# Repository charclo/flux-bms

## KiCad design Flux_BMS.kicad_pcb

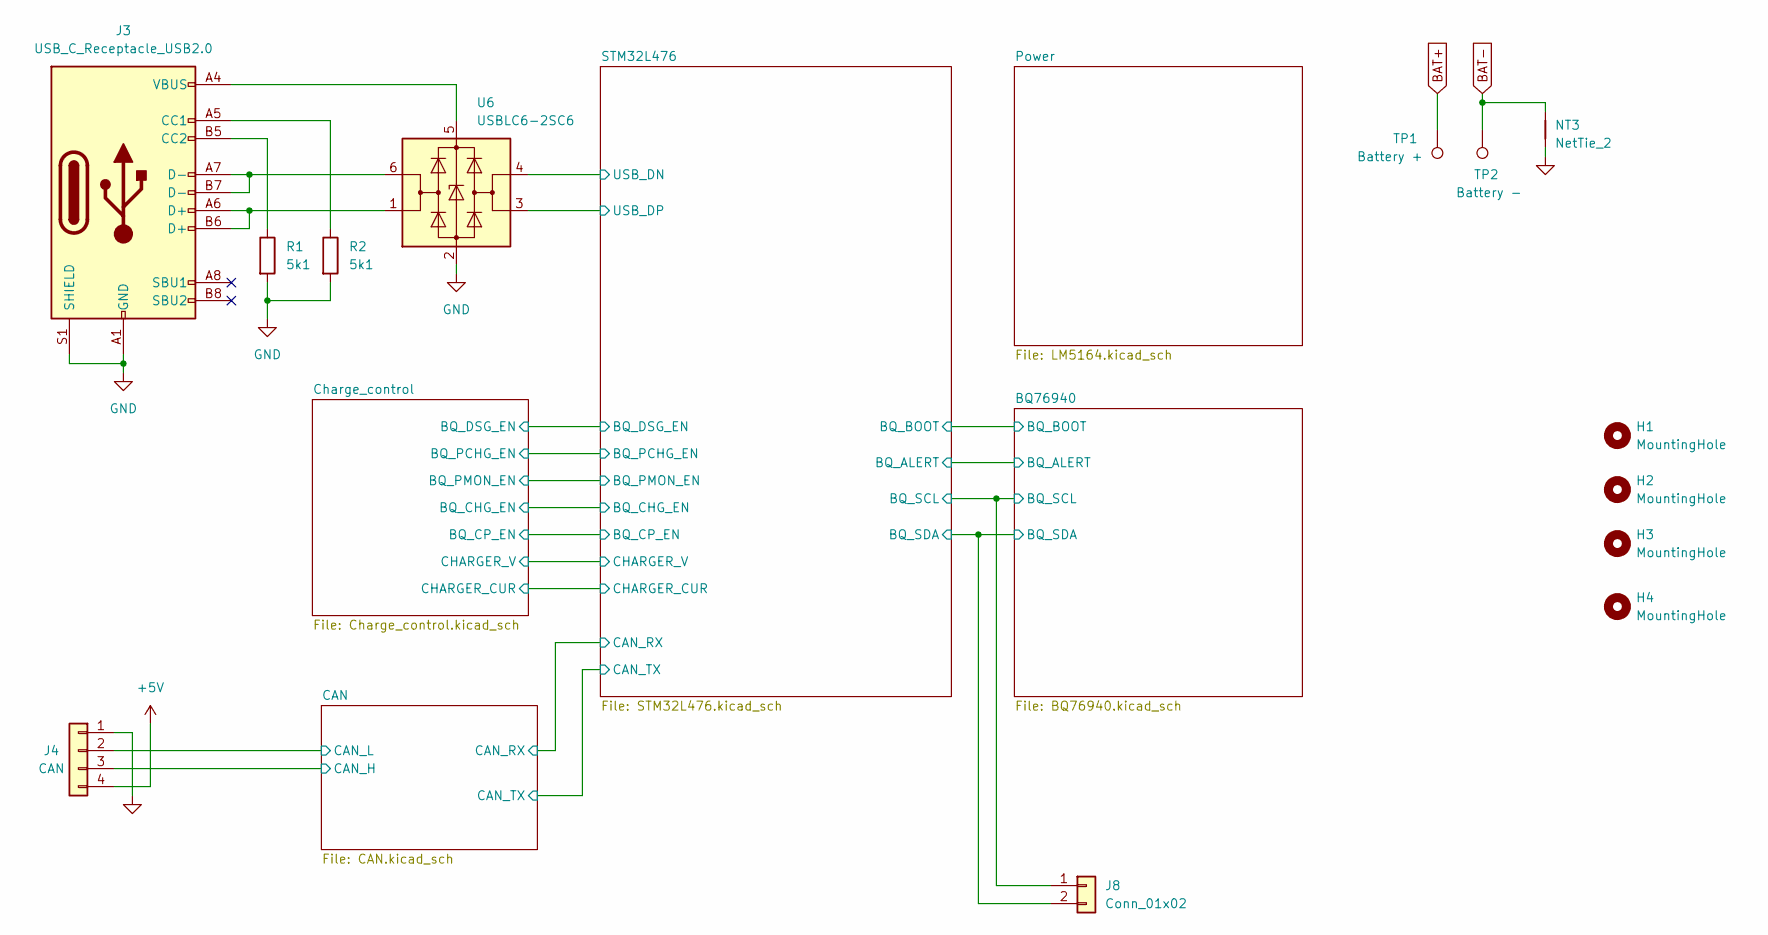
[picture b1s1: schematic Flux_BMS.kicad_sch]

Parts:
H1, H2, H3, H4: MountingHole; MountingHole_3.2mm_M3
J3: USB_C_Receptacle_USB2.0; USB_C_Receptacle_HRO_TYPE-C-31-M-12
J4: CAN; JST_PH_B4B-PH-K_1x04_P2.00mm_Vertical
J8: Conn_01x02; PinHeader_1x02_P2.54mm_Vertical
NT3: NetTie_2; NetTie-2_SMD_Pad2.0mm
R1, R2: 5k1; R_0805_2012Metric; LCSC C27834
TP1: Battery +; PAD
TP2: Battery -; PAD
U6: USBLC6-2SC6; SOT-23-6; LCSC C2827654

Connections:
+5V: J4.4; also elsewhere on the board
/BQ76940/BQ_SCL: J8.1; also elsewhere on the board
/BQ76940/BQ_SDA: J8.2; also elsewhere on the board
/CAN/CAN_H: J4.3; also elsewhere on the board
/CAN/CAN_L: J4.2; also elsewhere on the board
/STM32L476/USB_DN: U6.4 (I/O2); also elsewhere on the board
/STM32L476/USB_DP: U6.3 (I/O2); also elsewhere on the board
BAT+: TP1.1; also elsewhere on the board
BAT-: NT3.2, TP2.1; also elsewhere on the board
unnamed: J3.A5 (CC1), R2.1
unnamed: J3.B5 (CC2), R1.1
unnamed: J3.A6 (D+), J3.B6 (D+), U6.1 (I/O1)
unnamed: J3.A7 (D-), J3.B7 (D-), U6.6 (I/O1)
unnamed: J3.A4 (VBUS), J3.A9 (VBUS), J3.B4 (VBUS), J3.B9 (VBUS), U6.5 (VBUS)

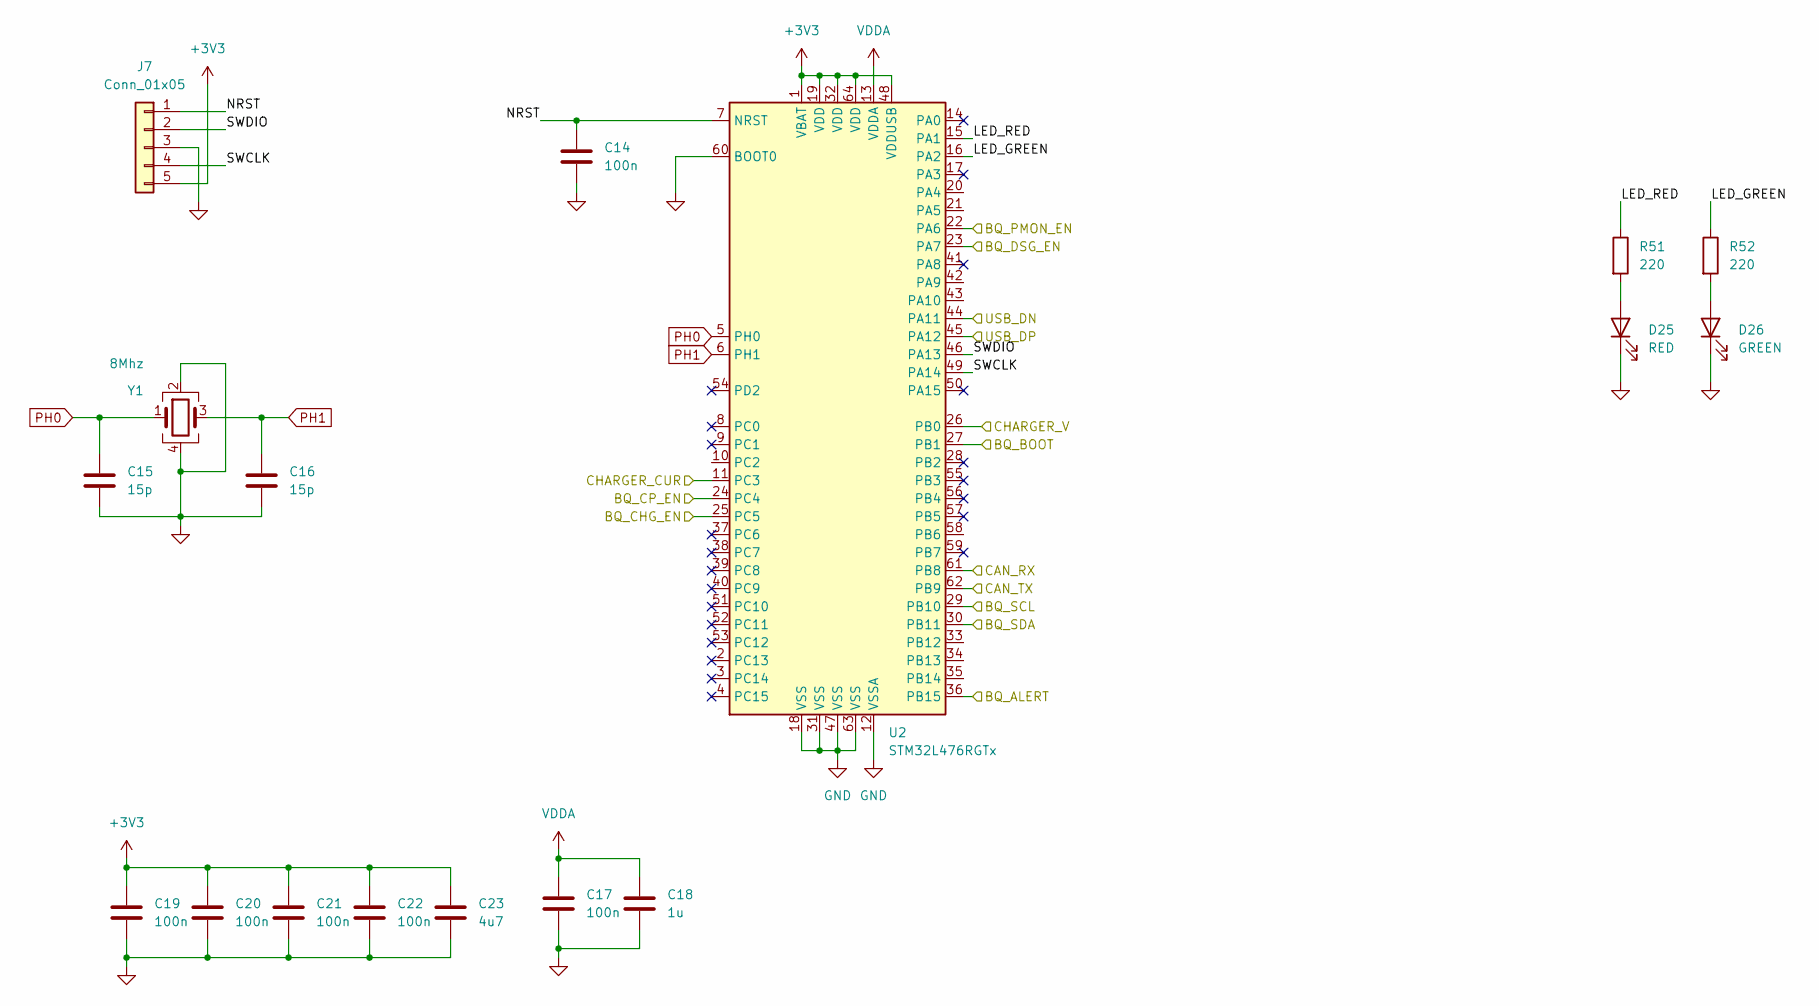
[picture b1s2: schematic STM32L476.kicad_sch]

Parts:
C14, C17, C19, C20, C21, C22: 100n; C_0603_1608Metric; LCSC C14663
C15, C16: 15p; C_0603_1608Metric; LCSC C1644
C18: 1u; C_0603_1608Metric; LCSC C15849
C23: 4u7; C_0603_1608Metric; LCSC C19666
D25: RED; LED_0805_2012Metric; LCSC C84256
D26: GREEN; LED_0805_2012Metric; LCSC C84256
J7: Conn_01x05; JST_PH_B5B-PH-K_1x05_P2.00mm_Vertical
R51, R52: 220; R_0805_2012Metric; LCSC C17557
U2: STM32L476RGTx; LQFP-64_10x10mm_P0.5mm; LCSC C92468
Y1: 8Mhz; Crystal_SMD_3225-4Pin_3.2x2.5mm; LCSC C2924619

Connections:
+3V3: C19.1, C20.1, C21.1, C22.1, C23.1, J7.5, U2.1 (VBAT), U2.19 (VDD), U2.32 (VDD), U2.48 (VDDUSB), U2.64 (VDD); also elsewhere on the board
/BQ76940/BQ_ALERT: U2.36 (PB15); also elsewhere on the board
/BQ76940/BQ_BOOT: U2.27 (PB1); also elsewhere on the board
/BQ76940/BQ_SCL: U2.29 (PB10); also elsewhere on the board
/BQ76940/BQ_SDA: U2.30 (PB11); also elsewhere on the board
/CAN/CAN_RX: U2.61 (PB8); also elsewhere on the board
/CAN/CAN_TX: U2.62 (PB9); also elsewhere on the board
/Charge_control/BQ_CHG_EN: U2.25 (PC5); also elsewhere on the board
/Charge_control/BQ_CP_EN: U2.24 (PC4); also elsewhere on the board
/Charge_control/BQ_DSG_EN: U2.23 (PA7); also elsewhere on the board
/Charge_control/BQ_PMON_EN: U2.22 (PA6); also elsewhere on the board
/Charge_control/CHARGER_CUR: U2.11 (PC3); also elsewhere on the board
/Charge_control/CHARGER_V: U2.26 (PB0); also elsewhere on the board
/STM32L476/LED_GREEN: R52.1, U2.16 (PA2)
/STM32L476/LED_RED: R51.1, U2.15 (PA1)
/STM32L476/NRST: C14.1, J7.1, U2.7 (NRST)
/STM32L476/SWCLK: J7.4, U2.49 (PA14)
/STM32L476/SWDIO: J7.2, U2.46 (PA13)
/STM32L476/USB_DN: U2.44 (PA11); also elsewhere on the board
/STM32L476/USB_DP: U2.45 (PA12); also elsewhere on the board
unnamed: D25.2 (A), R51.2
unnamed: D26.2 (A), R52.2
PH0: C15.1, U2.5 (PH0), Y1.1
PH1: C16.1, U2.6 (PH1), Y1.3
VDDA: C17.1, C18.1, U2.13 (VDDA)

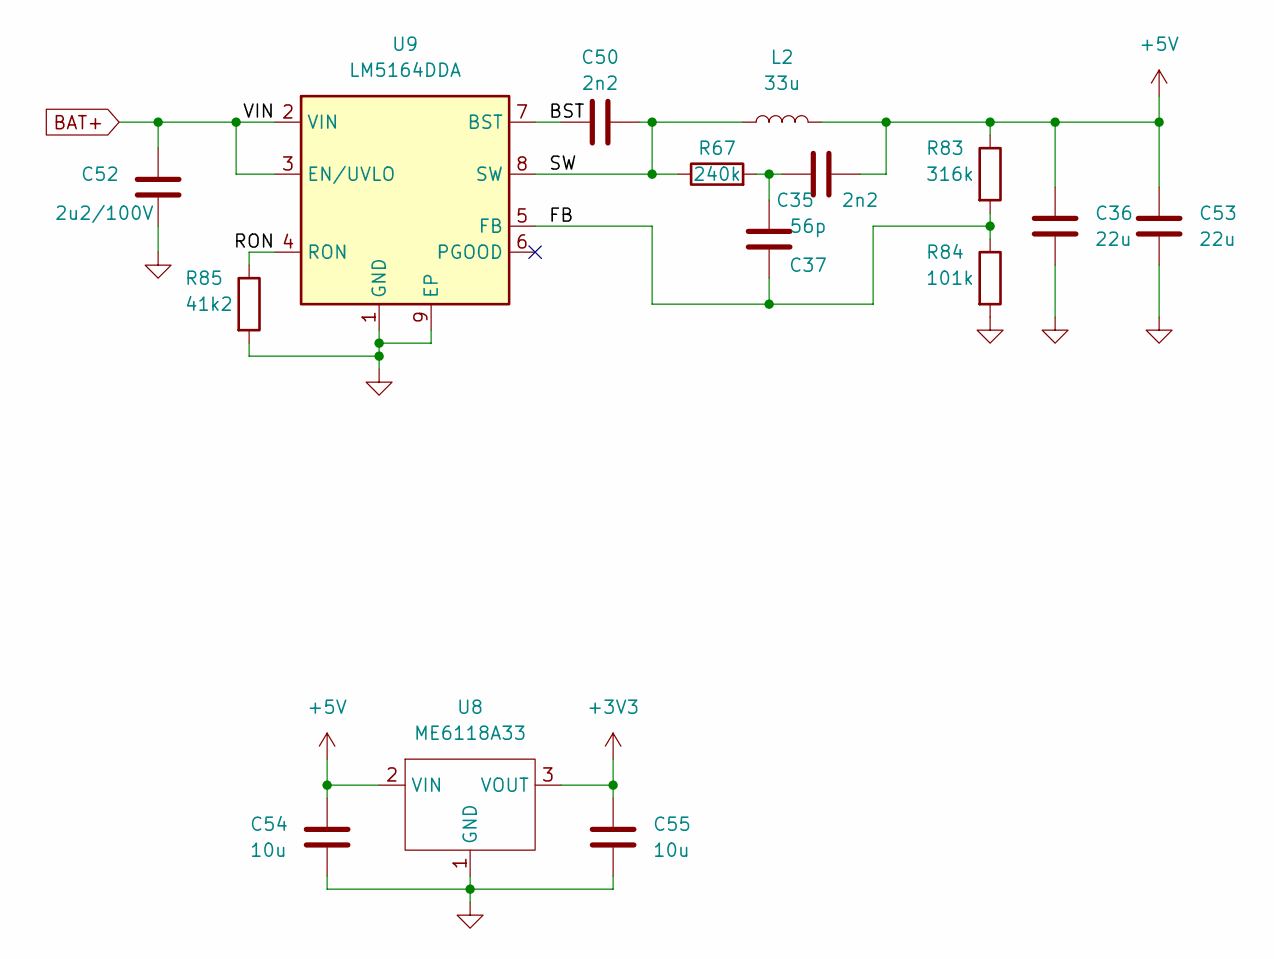
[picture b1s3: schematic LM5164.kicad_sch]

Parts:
C35, C50: 2n2; C_0603_1608Metric; LCSC C1604
C36, C53: 22u; C_0805_2012Metric; LCSC C45783
C37: 56p; C_0805_2012Metric; LCSC C14857
C52: 2u2/100V; C_1206_3216Metric; LCSC C577211
C54, C55: 10u; C_0805_2012Metric; LCSC C440198
L2: 33u; L_Taiyo-Yuden_NR-80xx
R67: 240k; R_0805_2012Metric; LCSC C416833
R83: 316k; R_0805_2012Metric; LCSC C367975
R84: 101k; R_0805_2012Metric; LCSC C17719
R85: 41k2; R_0805_2012Metric; LCSC C149504
U8: ME6118A33; SOT-89-3; LCSC C236721
U9: LM5164DDA; HSOP-8-1EP_3.9x4.9mm_P1.27mm_EP2.41x3.1mm_ThermalVias; LCSC C477928

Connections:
+3V3: C55.1, U8.3 (VOUT); also elsewhere on the board
+5V: C35.2, C36.1, C53.1, C54.1, L2.2, R83.1, U8.2 (VIN); also elsewhere on the board
/Power/BST: C50.1, U9.7 (BST)
/Power/FB: C37.1, R83.2, R84.1, U9.5 (FB)
/Power/RON: R85.1, U9.4 (RON)
/Power/SW: C50.2, L2.1, R67.1, U9.8 (SW)
BAT+: C52.1, U9.2 (VIN), U9.3 (EN/UVLO); also elsewhere on the board
unnamed: C35.1, C37.2, R67.2

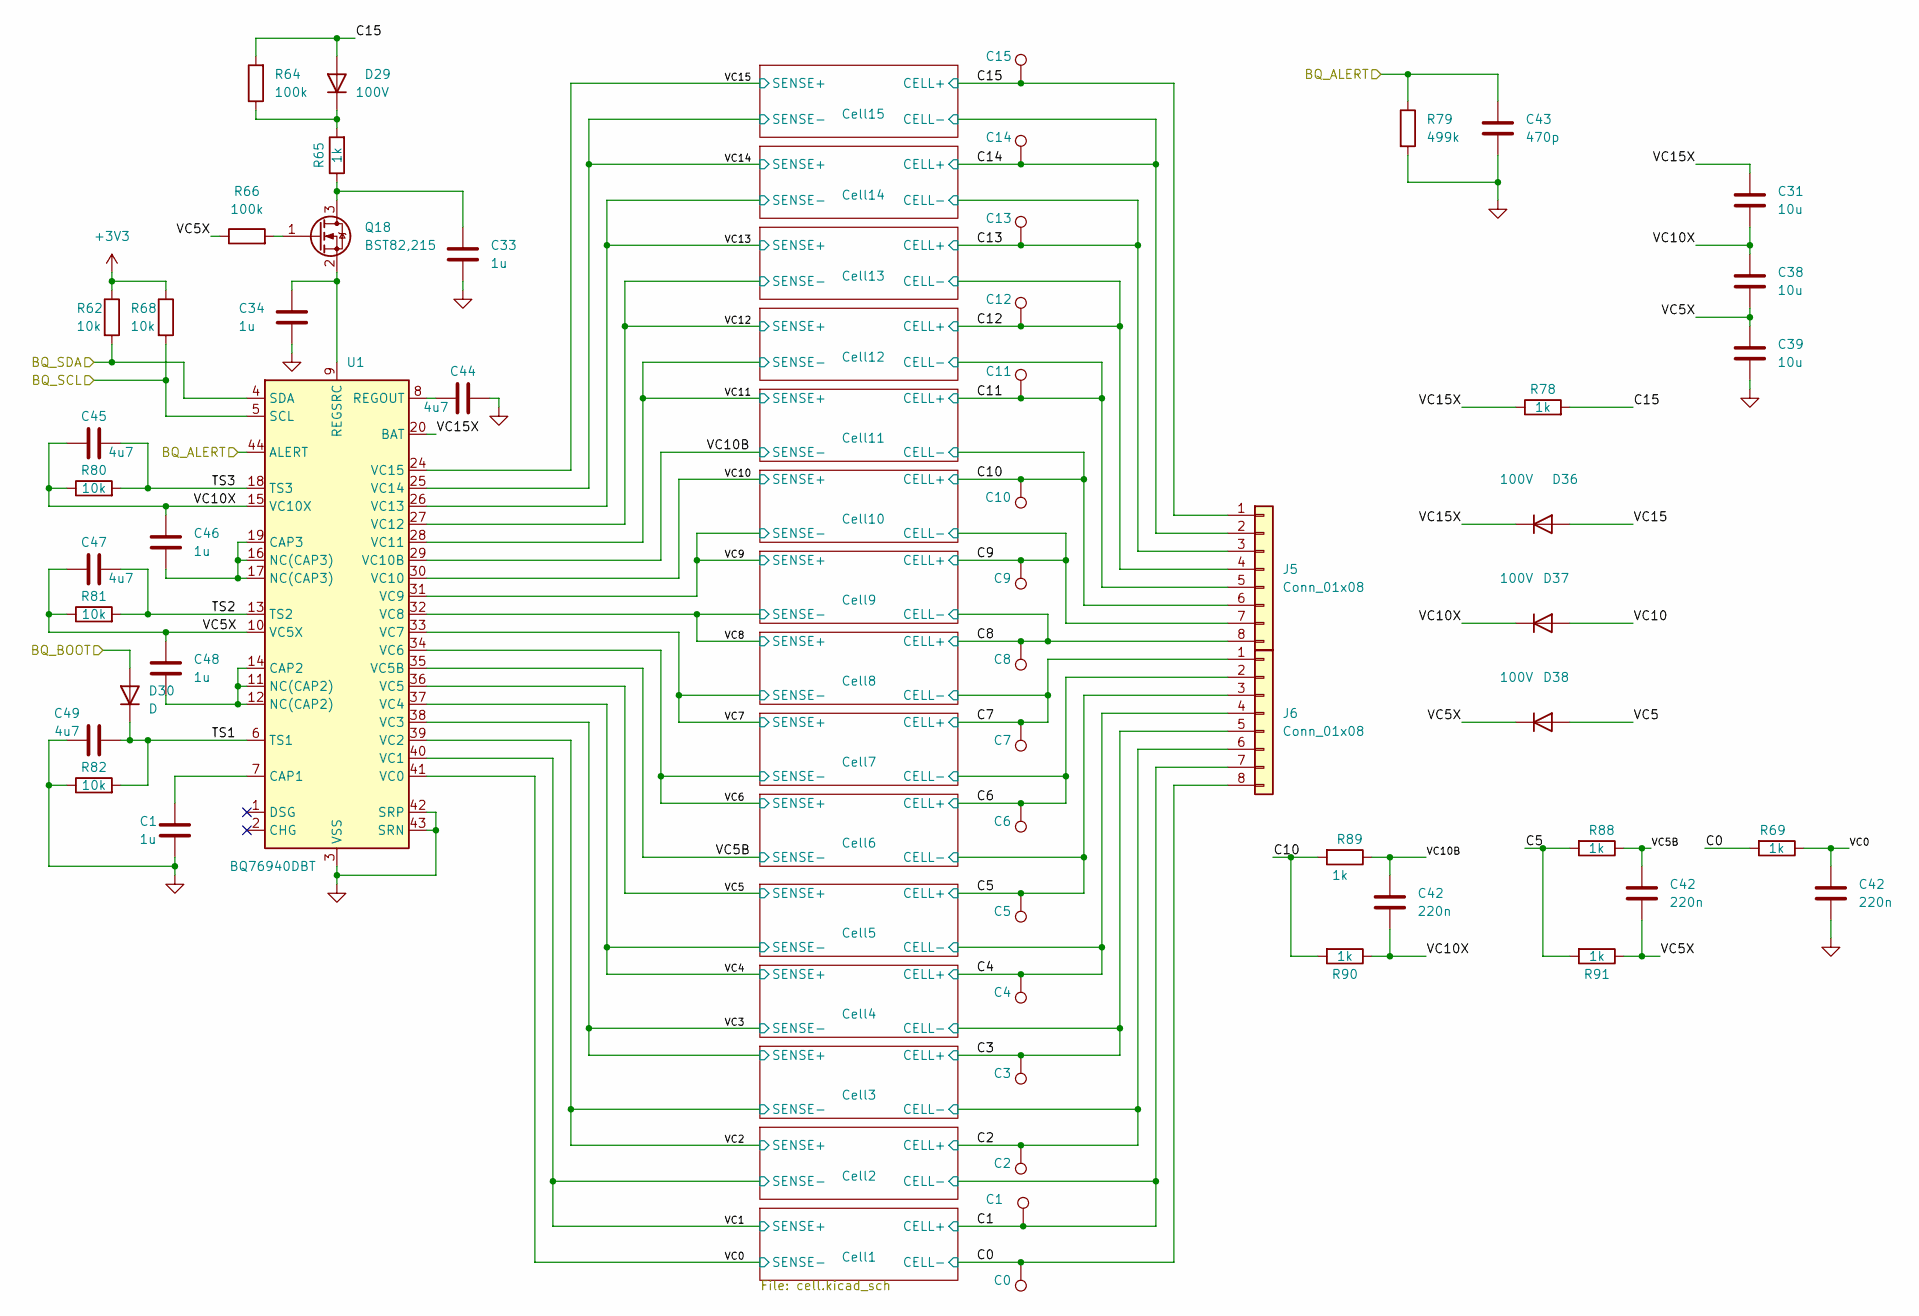
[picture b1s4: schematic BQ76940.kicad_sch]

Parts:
C1, C33, C34, C46, C48: 1u; C_0805_2012Metric; LCSC C28323
C31, C38, C39: 10u; C_0805_2012Metric; LCSC C440198
C42: 220n; C_0805_2012Metric; LCSC C5378
C43: 470p; C_0805_2012Metric; LCSC C1743
C44, C45, C47, C49: 4u7; C_0805_2012Metric; LCSC C440198
D29, D36, D37, D38: 100V; D_SOD-123; LCSC C83528
D30: D; D_SOD-323_HandSoldering
J5, J6: Conn_01x08; JST_PH_S8B-PH-K_1x08_P2.00mm_Horizontal
Q18: BST82,215; SOT-23; LCSC C426800
R62, R68, R82: 10k; R_0805_2012Metric; LCSC C17414
R64, R66: 100k; R_0805_2012Metric; LCSC C149504
R65, R69, R78, R88, R89, R90, R91: 1k; R_0805_2012Metric; LCSC C17513
R79: 499k; R_0805_2012Metric; LCSC C2960934
R80, R81: 10k; JST_PH_B2B-PH-K_1x02_P2.00mm_Vertical
TP7: C15; TestPoint_THTPad_D1.0mm_Drill0.5mm
TP8: C14; TestPoint_THTPad_D1.0mm_Drill0.5mm
TP9: C13; TestPoint_THTPad_D1.0mm_Drill0.5mm
TP10: C12; TestPoint_THTPad_D1.0mm_Drill0.5mm
TP11: C11; TestPoint_THTPad_D1.0mm_Drill0.5mm
TP12: C10; TestPoint_THTPad_D1.0mm_Drill0.5mm
TP13: C9; TestPoint_THTPad_D1.0mm_Drill0.5mm
TP14: C8; TestPoint_THTPad_D1.0mm_Drill0.5mm
TP15: C7; TestPoint_THTPad_D1.0mm_Drill0.5mm
TP16: C6; TestPoint_THTPad_D1.0mm_Drill0.5mm
TP17: C5; TestPoint_THTPad_D1.0mm_Drill0.5mm
TP18: C4; TestPoint_THTPad_D1.0mm_Drill0.5mm
TP19: C3; TestPoint_THTPad_D1.0mm_Drill0.5mm
TP20: C2; TestPoint_THTPad_D1.0mm_Drill0.5mm
TP21: C1; TestPoint_THTPad_D1.0mm_Drill0.5mm
TP22: C0; TestPoint_THTPad_D1.0mm_Drill0.5mm
U1: BQ76940DBT; TSSOP-44_4.4x11.2mm_P0.5mm; LCSC C368606

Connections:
+3V3: R62.1, R68.1; also elsewhere on the board
/BQ76940/BQ_ALERT: C43.1, R79.1, U1.44 (ALERT); also elsewhere on the board
/BQ76940/BQ_BOOT: D30.2 (A); also elsewhere on the board
/BQ76940/BQ_SCL: R68.2, U1.5 (SCL); also elsewhere on the board
/BQ76940/BQ_SDA: R62.2, U1.4 (SDA); also elsewhere on the board
/BQ76940/C0: J6.8, R69.2, TP22.1; also elsewhere on the board
/BQ76940/C1: J6.7, TP21.1; also elsewhere on the board
/BQ76940/C2: J6.6, TP20.1; also elsewhere on the board
/BQ76940/C3: J6.5, TP19.1; also elsewhere on the board
/BQ76940/C4: J6.4, TP18.1; also elsewhere on the board
/BQ76940/C5: J6.3, R88.2, R91.2, TP17.1; also elsewhere on the board
/BQ76940/C6: J6.2, TP16.1; also elsewhere on the board
/BQ76940/C7: J6.1, TP15.1; also elsewhere on the board
/BQ76940/C8: J5.8, TP14.1; also elsewhere on the board
/BQ76940/C9: J5.7, TP13.1; also elsewhere on the board
/BQ76940/C10: J5.6, R89.2, R90.2, TP12.1; also elsewhere on the board
/BQ76940/C11: J5.5, TP11.1; also elsewhere on the board
/BQ76940/C12: J5.4, TP10.1; also elsewhere on the board
/BQ76940/C13: J5.3, TP9.1; also elsewhere on the board
/BQ76940/C14: J5.2, TP8.1; also elsewhere on the board
/BQ76940/C15: D29.2 (A), J5.1, R64.2, R78.2, TP7.1; also elsewhere on the board
/BQ76940/TS1: C49.2, D30.1 (K), R82.2, U1.6 (TS1)
/BQ76940/TS2: C47.2, R81.2, U1.13 (TS2)
/BQ76940/TS3: C45.2, R80.2, U1.18 (TS3)
/BQ76940/VC1: U1.40 (VC1); also elsewhere on the board
/BQ76940/VC2: U1.39 (VC2); also elsewhere on the board
/BQ76940/VC3: U1.38 (VC3); also elsewhere on the board
/BQ76940/VC4: U1.37 (VC4); also elsewhere on the board
/BQ76940/VC5: D38.2 (A), U1.36 (VC5); also elsewhere on the board
/BQ76940/VC6: U1.34 (VC6); also elsewhere on the board
/BQ76940/VC7: U1.33 (VC7); also elsewhere on the board
/BQ76940/VC8: U1.32 (VC8); also elsewhere on the board
/BQ76940/VC9: U1.31 (VC9); also elsewhere on the board
/BQ76940/VC10: D37.2 (A), U1.30 (VC10); also elsewhere on the board
/BQ76940/VC11: U1.28 (VC11); also elsewhere on the board
/BQ76940/VC12: U1.27 (VC12); also elsewhere on the board
/BQ76940/VC13: U1.26 (VC13); also elsewhere on the board
/BQ76940/VC15X: C31.1, D36.1 (K), R78.1, U1.20 (BAT)
unnamed: D29.1 (K), R64.1, R65.2
unnamed: C33.1, Q18.3 (D), R65.1
unnamed: Q18.1 (G), R66.2
unnamed: C34.1, Q18.2 (S), U1.9 (REGSRC)
unnamed: C1.1, U1.7 (CAP1)
unnamed: C48.2, U1.11 (NC(CAP2)), U1.12 (NC(CAP2)), U1.14 (CAP2)
unnamed: C46.2, U1.16 (NC(CAP3)), U1.17 (NC(CAP3)), U1.19 (CAP3)
unnamed: C44.1, U1.8 (REGOUT)

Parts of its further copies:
C2, C3, C4, C5, C6, C7, C8, C9, C10, C11, C12, C13, C24, C41, C51, C56, C57: 220n; C_0805_2012Metric; LCSC C5378

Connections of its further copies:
/BQ76940/VC1: C10.2, C11.1; also elsewhere on the board
/BQ76940/VC2: C9.2, C10.1; also elsewhere on the board
/BQ76940/VC3: C9.1, C24.2; also elsewhere on the board
/BQ76940/VC4: C7.2, C24.1; also elsewhere on the board
/BQ76940/VC5: C7.1; also elsewhere on the board
/BQ76940/VC6: C5.2, C6.1; also elsewhere on the board
/BQ76940/VC7: C4.2, C5.1; also elsewhere on the board
/BQ76940/VC8: C3.2, C4.1; also elsewhere on the board
/BQ76940/VC9: C2.2, C3.1; also elsewhere on the board
/BQ76940/VC10: C2.1; also elsewhere on the board
/BQ76940/VC11: C8.2, C13.1; also elsewhere on the board
/BQ76940/VC12: C8.1, C12.2; also elsewhere on the board
/BQ76940/VC13: C12.1, C41.2; also elsewhere on the board

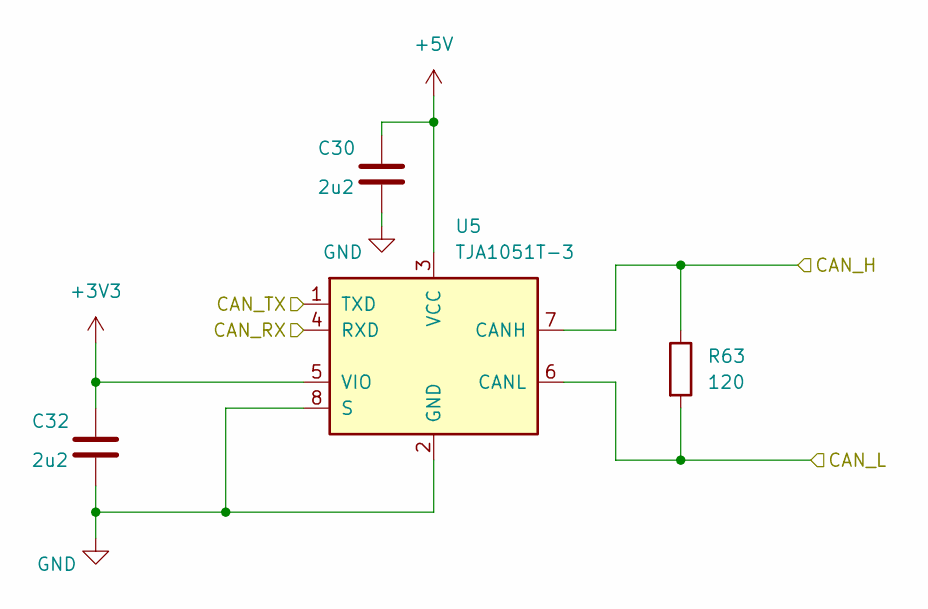
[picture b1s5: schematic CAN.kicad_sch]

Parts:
C30, C32: 2u2; C_0603_1608Metric; LCSC C23630
R63: 120; R_0805_2012Metric; LCSC C17437
U5: TJA1051T-3; SOIC-8_3.9x4.9mm_P1.27mm; LCSC c58988

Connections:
+3V3: C32.1, U5.5 (VIO); also elsewhere on the board
+5V: C30.1, U5.3 (VCC); also elsewhere on the board
/CAN/CAN_H: R63.1, U5.7 (CANH); also elsewhere on the board
/CAN/CAN_L: R63.2, U5.6 (CANL); also elsewhere on the board
/CAN/CAN_RX: U5.4 (RXD); also elsewhere on the board
/CAN/CAN_TX: U5.1 (TXD); also elsewhere on the board

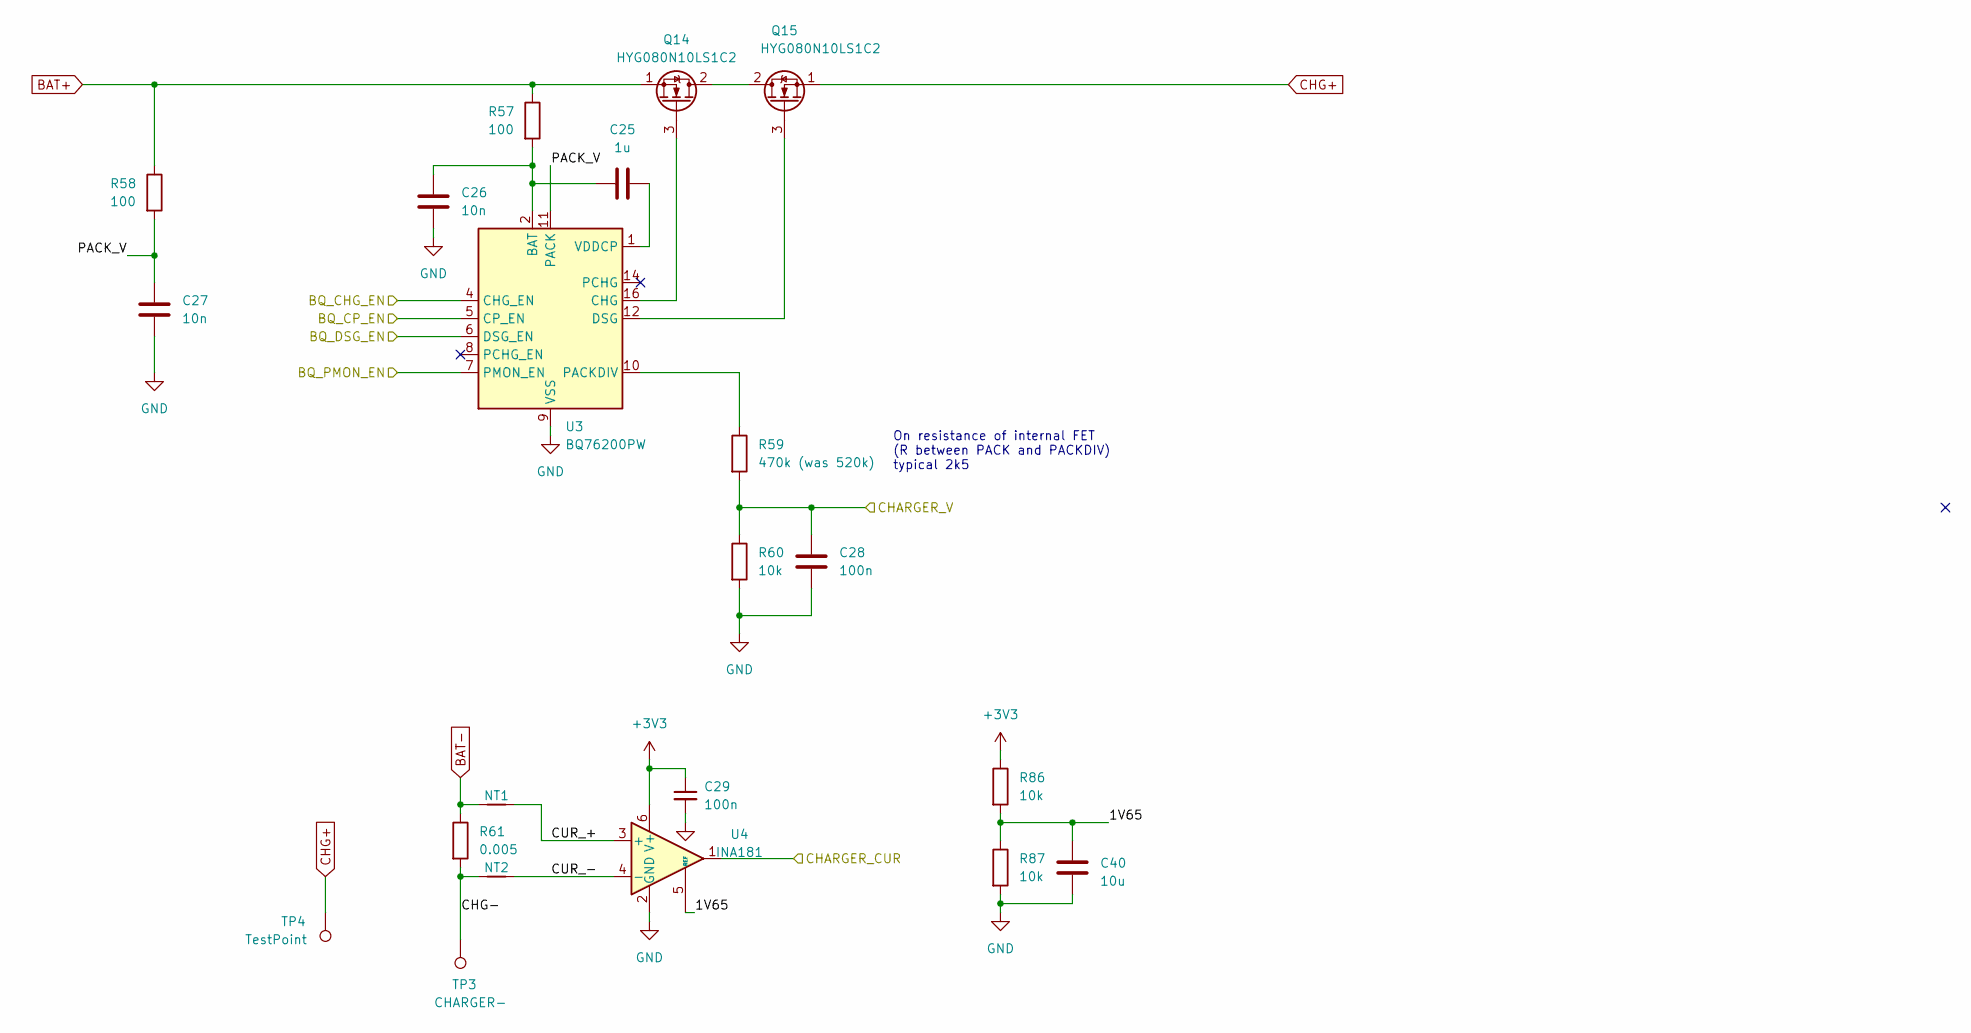
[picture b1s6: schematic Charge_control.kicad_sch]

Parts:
C25: 1u; C_0603_1608Metric; LCSC C15849
C26: 10n; C_0603_1608Metric; LCSC C57112
C27: 10n; C_0805_2012Metric; LCSC C1710
C28: 100n; C_0805_2012Metric; LCSC C28233
C29: 100n; C_0603_1608Metric; LCSC C14663
C40: 10u; C_0805_2012Metric; LCSC C440198
NT1, NT2: NetTie_2; NetTie-2_SMD_Pad0.5mm
Q14, Q15: HYG080N10LS1C2; TRANS_BSC076N06NS3-G; LCSC C3011225
R57, R58: 100; R_0805_2012Metric; LCSC C17408
R59: 470k (was 520k); R_0805_2012Metric; LCSC C17709
R60: 10k; R_0805_2012Metric; LCSC C17414
R61: 0.005; R_2512_6332Metric; LCSC C2903465
R86, R87: 10k; R_0603_1608Metric; LCSC C17414
TP3: CHARGER-; PAD
TP4: TestPoint; PAD
U3: BQ76200PW; TSSOP-16_4.4x5mm_P0.65mm; LCSC C216213
U4: INA181; SOT-23-6

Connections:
+3V3: C29.1, R86.1, U4.6 (V+); also elsewhere on the board
/Charge_control/1V65: C40.1, R86.2, R87.1, U4.5 (REF)
/Charge_control/BQ_CHG_EN: U3.4 (CHG_EN); also elsewhere on the board
/Charge_control/BQ_CP_EN: U3.5 (CP_EN); also elsewhere on the board
/Charge_control/BQ_DSG_EN: U3.6 (DSG_EN); also elsewhere on the board
/Charge_control/BQ_PMON_EN: U3.7 (PMON_EN); also elsewhere on the board
/Charge_control/CHARGER_CUR: U4.1; also elsewhere on the board
/Charge_control/CHARGER_V: C28.2, R59.2, R60.1; also elsewhere on the board
/Charge_control/CHG-: NT2.1, R61.2, TP3.1
/Charge_control/CUR_+: NT1.2, U4.3 (+)
/Charge_control/CUR_-: NT2.2, U4.4 (-)
/Charge_control/PACK_V: C27.2, R58.2, U3.11 (PACK)
BAT+: Q14.1 (S), R57.1, R58.1; also elsewhere on the board
BAT-: NT1.1, R61.1; also elsewhere on the board
CHG+: Q15.1 (S), TP4.1
unnamed: Q14.2 (D), Q15.2 (D)
unnamed: Q14.3 (G), U3.16 (CHG)
unnamed: Q15.3 (G), U3.12 (DSG)
unnamed: C25.1, C26.2, R57.2, U3.2 (BAT)
unnamed: R59.1, U3.10 (PACKDIV)
unnamed: C25.2, U3.1 (VDDCP)

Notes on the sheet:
On resistance of internal FET (R between PACK and PACKDIV) typical 2k5

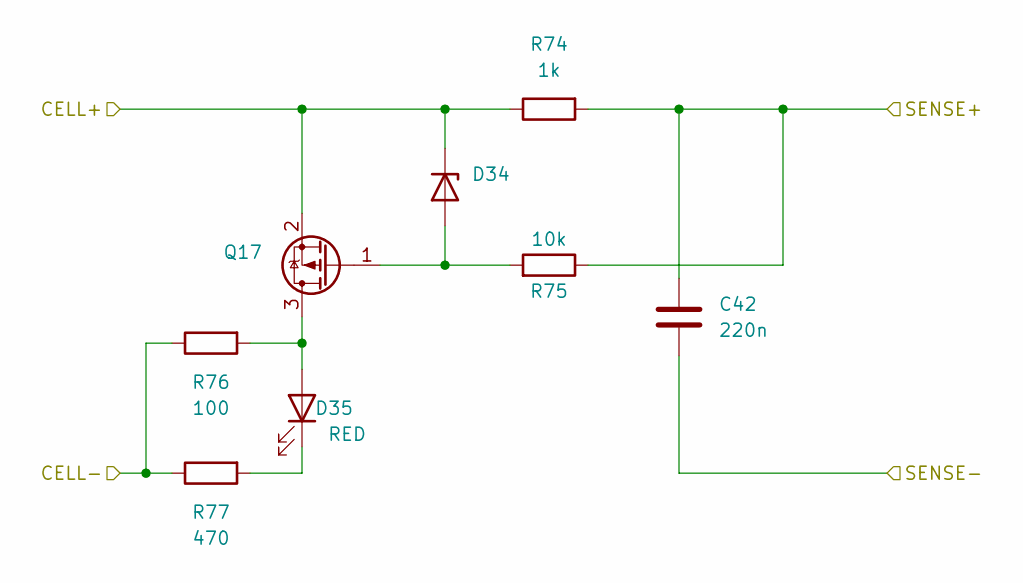
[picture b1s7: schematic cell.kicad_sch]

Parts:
C42: 220n; C_0805_2012Metric; LCSC C5378
D34: D_SOD-323_HandSoldering; LCSC C2845017
D35: RED; LED_0805_2012Metric; LCSC C84256
Q17: SOT-23; LCSC C8492
R74: 1k; R_0805_2012Metric; LCSC C17513
R75: 10k; R_0805_2012Metric; LCSC C17414
R76: 100; R_2512_6332Metric; LCSC C2934070
R77: 470; R_0805_2012Metric; LCSC C17710

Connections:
/BQ76940/C14: R76.1, R77.1; also elsewhere on the board
/BQ76940/C15: D34.1 (K), Q17.2 (S), R74.1; also elsewhere on the board
unnamed: D34.2 (A), Q17.1 (G), R75.2
unnamed: D35.2 (A), Q17.3 (D), R76.2
unnamed: D35.1 (K), R77.2

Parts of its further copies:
C2, C3, C4, C5, C6, C7, C8, C9, C10, C11, C12, C13, C24, C41: 220n; C_0805_2012Metric; LCSC C5378
D1, D3, D5, D7, D9, D11, D13, D15, D17, D19, D21, D23, D27, D32: D_SOD-323_HandSoldering; LCSC C2845017
D2, D4, D6, D8, D10, D12, D14, D16, D18, D20, D22, D24, D28, D33: RED; LED_0805_2012Metric; LCSC C84256
Q1, Q2, Q3, Q4, Q5, Q6, Q7, Q8, Q9, Q10, Q11, Q12, Q13, Q16: SOT-23; LCSC C8492
R3, R7, R11, R15, R19, R23, R27, R31, R35, R39, R43, R47, R53, R70: 1k; R_0805_2012Metric; LCSC C17513
R4, R8, R12, R16, R20, R24, R28, R32, R36, R40, R44, R48, R54, R71: 10k; R_0805_2012Metric; LCSC C17414
R5, R9, R13, R17, R21, R25, R29, R33, R37, R41, R45, R49, R55, R72: 100; R_2512_6332Metric; LCSC C2934070
R6, R10, R14, R18, R22, R26, R30, R34, R38, R42, R46, R50, R56, R73: 470; R_0805_2012Metric; LCSC C17710

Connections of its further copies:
/BQ76940/C0: R41.1, R42.1; also elsewhere on the board
/BQ76940/C1: D19.1 (K), Q10.2 (S), R37.1, R38.1, R39.1; also elsewhere on the board
/BQ76940/C2: D17.1 (K), Q9.2 (S), R33.1, R34.1, R35.1; also elsewhere on the board
/BQ76940/C3: D15.1 (K), Q8.2 (S), R31.1, R55.1, R56.1; also elsewhere on the board
/BQ76940/C4: D27.1 (K), Q13.2 (S), R25.1, R26.1, R53.1; also elsewhere on the board
/BQ76940/C5: D11.1 (K), Q6.2 (S), R21.1, R22.1, R23.1; also elsewhere on the board
/BQ76940/C6: D9.1 (K), Q5.2 (S), R17.1, R18.1, R19.1; also elsewhere on the board
/BQ76940/C7: D7.1 (K), Q4.2 (S), R13.1, R14.1, R15.1; also elsewhere on the board
/BQ76940/C8: D5.1 (K), Q3.2 (S), R9.1, R10.1, R11.1; also elsewhere on the board
/BQ76940/C9: D3.1 (K), Q2.2 (S), R5.1, R6.1, R7.1; also elsewhere on the board
/BQ76940/C10: D1.1 (K), Q1.2 (S), R3.1, R49.1, R50.1; also elsewhere on the board
/BQ76940/C11: D23.1 (K), Q12.2 (S), R29.1, R30.1, R47.1; also elsewhere on the board
/BQ76940/C12: D13.1 (K), Q7.2 (S), R27.1, R45.1, R46.1; also elsewhere on the board
/BQ76940/C13: D21.1 (K), Q11.2 (S), R43.1, R72.1, R73.1; also elsewhere on the board
/BQ76940/C14: D32.1 (K), Q16.2 (S), R70.1; also elsewhere on the board
/BQ76940/VC1: C10.2, C11.1, R39.2, R40.1; also elsewhere on the board
/BQ76940/VC2: C9.2, C10.1, R35.2, R36.1; also elsewhere on the board
/BQ76940/VC3: C9.1, C24.2, R31.2, R32.1; also elsewhere on the board
/BQ76940/VC4: C7.2, C24.1, R53.2, R54.1; also elsewhere on the board
/BQ76940/VC5: C7.1, R23.2, R24.1; also elsewhere on the board
/BQ76940/VC6: C5.2, C6.1, R19.2, R20.1; also elsewhere on the board
/BQ76940/VC7: C4.2, C5.1, R15.2, R16.1; also elsewhere on the board
/BQ76940/VC8: C3.2, C4.1, R11.2, R12.1; also elsewhere on the board
/BQ76940/VC9: C2.2, C3.1, R7.2, R8.1; also elsewhere on the board
/BQ76940/VC10: C2.1, R3.2, R4.1; also elsewhere on the board
/BQ76940/VC11: C8.2, C13.1, R47.2, R48.1; also elsewhere on the board
/BQ76940/VC12: C8.1, C12.2, R27.2, R28.1; also elsewhere on the board
/BQ76940/VC13: C12.1, C41.2, R43.2, R44.1; also elsewhere on the board
unnamed: D1.2 (A), Q1.1 (G), R4.2
unnamed: D2.2 (A), Q1.3 (D), R5.2
unnamed: D2.1 (K), R6.2
unnamed: D3.2 (A), Q2.1 (G), R8.2
unnamed: D4.2 (A), Q2.3 (D), R9.2
unnamed: D4.1 (K), R10.2
unnamed: D5.2 (A), Q3.1 (G), R12.2
unnamed: D6.2 (A), Q3.3 (D), R13.2
unnamed: D6.1 (K), R14.2
unnamed: D7.2 (A), Q4.1 (G), R16.2
unnamed: D8.2 (A), Q4.3 (D), R17.2
unnamed: D8.1 (K), R18.2
unnamed: D9.2 (A), Q5.1 (G), R20.2
unnamed: D10.2 (A), Q5.3 (D), R21.2
unnamed: D10.1 (K), R22.2
unnamed: D11.2 (A), Q6.1 (G), R24.2
unnamed: D12.2 (A), Q6.3 (D), R25.2
unnamed: D12.1 (K), R26.2
unnamed: D13.2 (A), Q7.1 (G), R28.2
unnamed: D14.2 (A), Q7.3 (D), R29.2
unnamed: D14.1 (K), R30.2
unnamed: D15.2 (A), Q8.1 (G), R32.2
unnamed: D16.2 (A), Q8.3 (D), R33.2
unnamed: D16.1 (K), R34.2
unnamed: D17.2 (A), Q9.1 (G), R36.2
unnamed: D18.2 (A), Q9.3 (D), R37.2
unnamed: D18.1 (K), R38.2
unnamed: D19.2 (A), Q10.1 (G), R40.2
unnamed: D20.2 (A), Q10.3 (D), R41.2
unnamed: D20.1 (K), R42.2
unnamed: D21.2 (A), Q11.1 (G), R44.2
unnamed: D22.2 (A), Q11.3 (D), R45.2
unnamed: D22.1 (K), R46.2
unnamed: D23.2 (A), Q12.1 (G), R48.2
unnamed: D24.2 (A), Q12.3 (D), R49.2
unnamed: D24.1 (K), R50.2
unnamed: D27.2 (A), Q13.1 (G), R54.2
unnamed: D28.2 (A), Q13.3 (D), R55.2
unnamed: D28.1 (K), R56.2
unnamed: D32.2 (A), Q16.1 (G), R71.2
unnamed: D33.2 (A), Q16.3 (D), R72.2
unnamed: D33.1 (K), R73.2

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
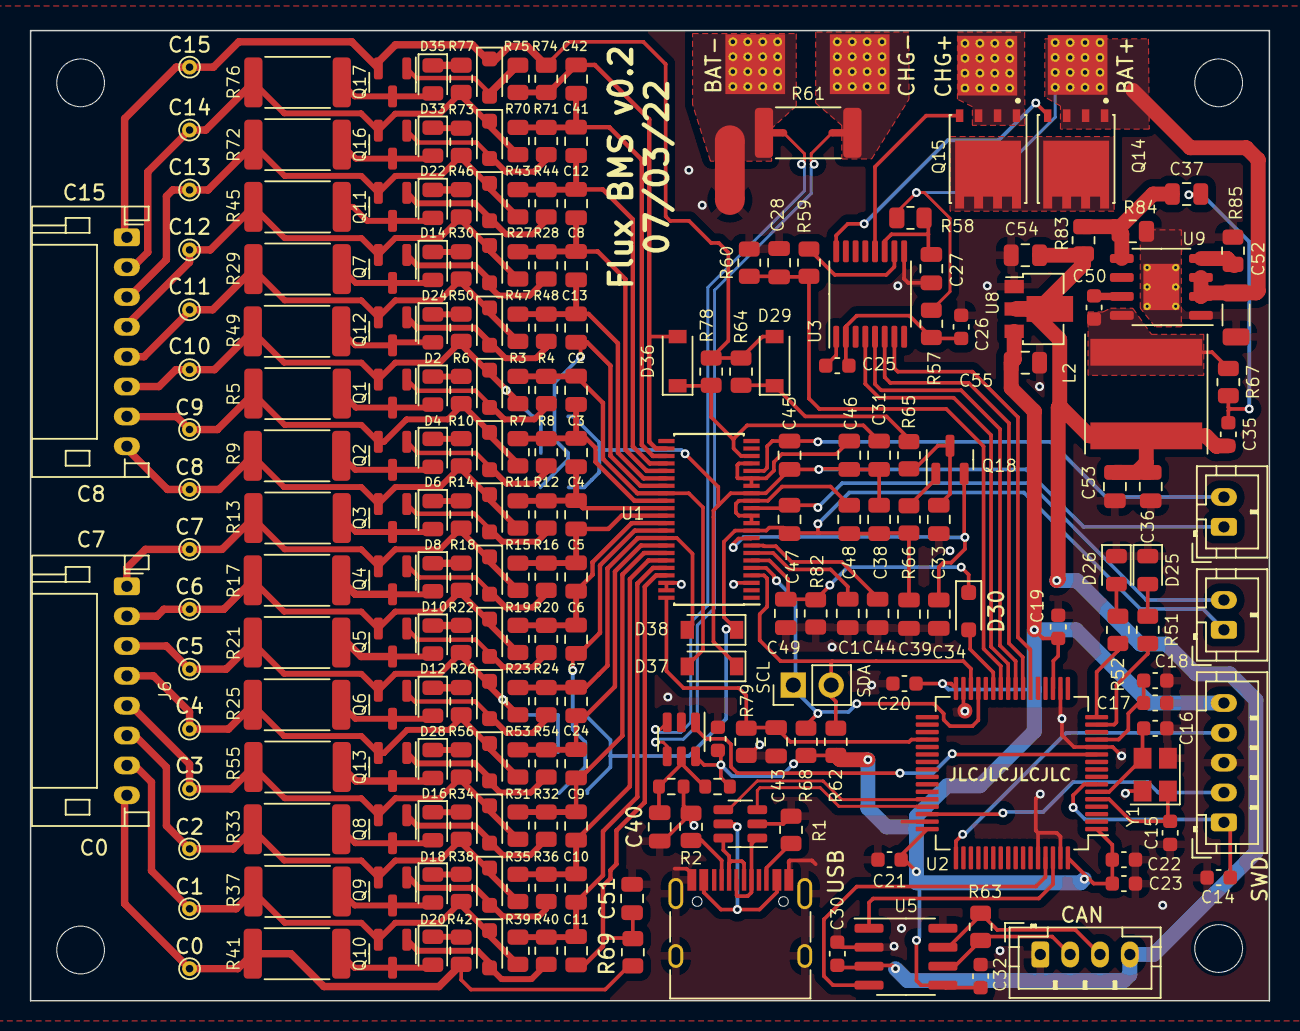
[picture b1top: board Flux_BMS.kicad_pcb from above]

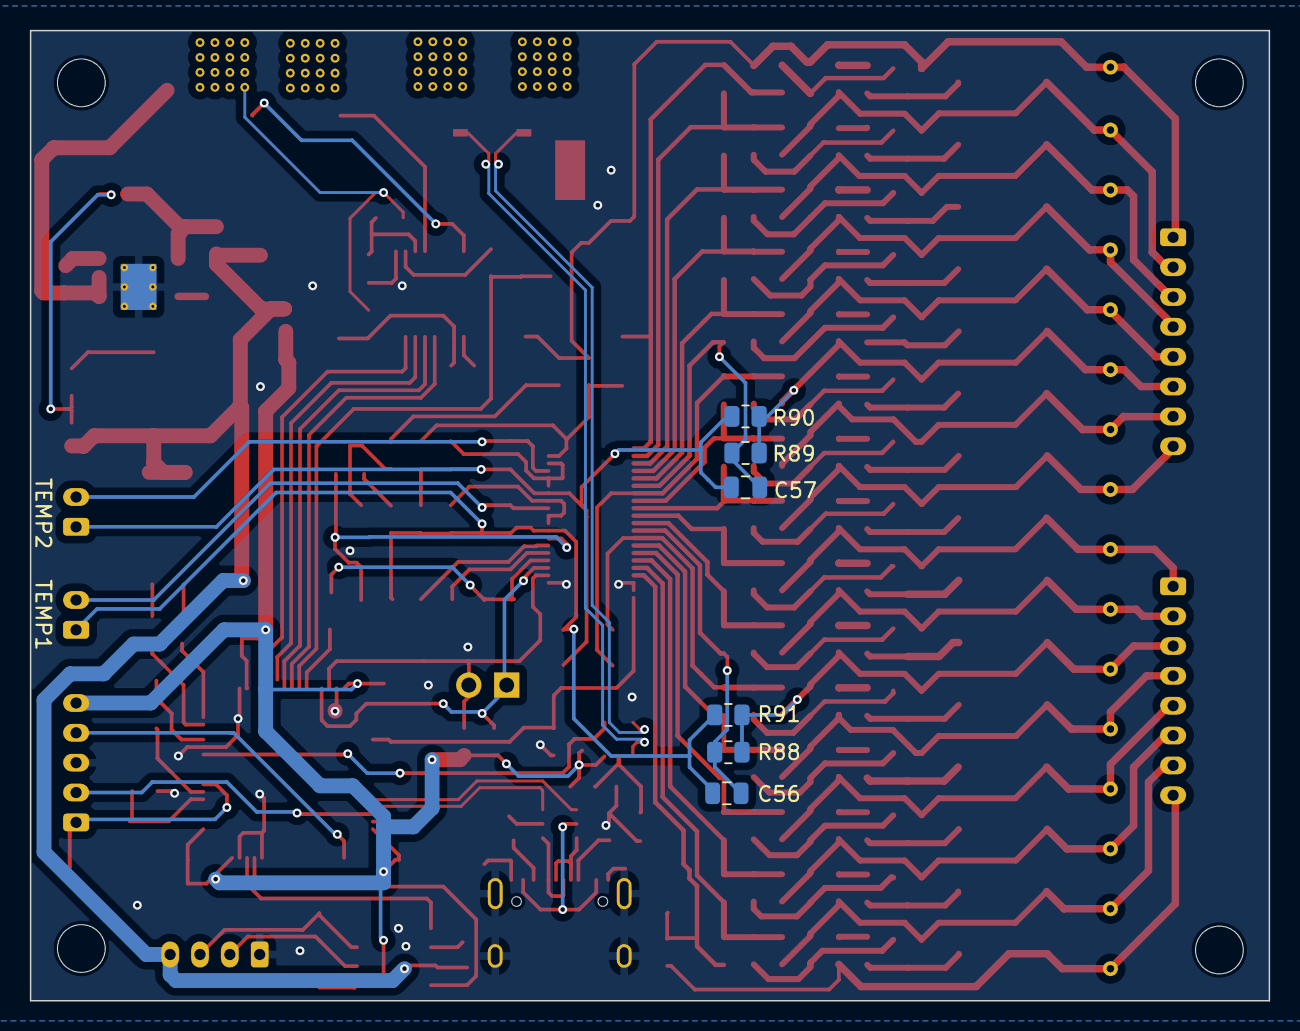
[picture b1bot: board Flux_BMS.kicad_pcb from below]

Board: 4 copper layers, 83.0 x 65.0 mm, 246 parts (6 on the bottom side), 146 nets.

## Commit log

2022-06-28 Added ltc6811
2022-06-29 caps moved around ltc
2022-07-04 Added part of power schematic
2022-09-09 routed most tracks
2022-09-19 new board dimensions
2022-09-21 placed bleed resistors
2022-09-26 power changes
2022-12-09 before meeting
2023-01-13 almost ready to order
2023-02-20 before switching to kicad 7
2023-10-15 V0.2
